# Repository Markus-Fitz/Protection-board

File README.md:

# Protection-board
 Speaker-protection board for power amplifier.

# Description
 The board includes a relay that connects or disconnects the speakers from the amplifiers. The circuit includes a delay function to avoid initial transients to damage the speakers, a DC-detection to protect the speakers in case of a failing output stage or wrong DC-adjustment and a temperature-sensing circuit which disconnects the speakers from the amplifiers in case of overtemperature.

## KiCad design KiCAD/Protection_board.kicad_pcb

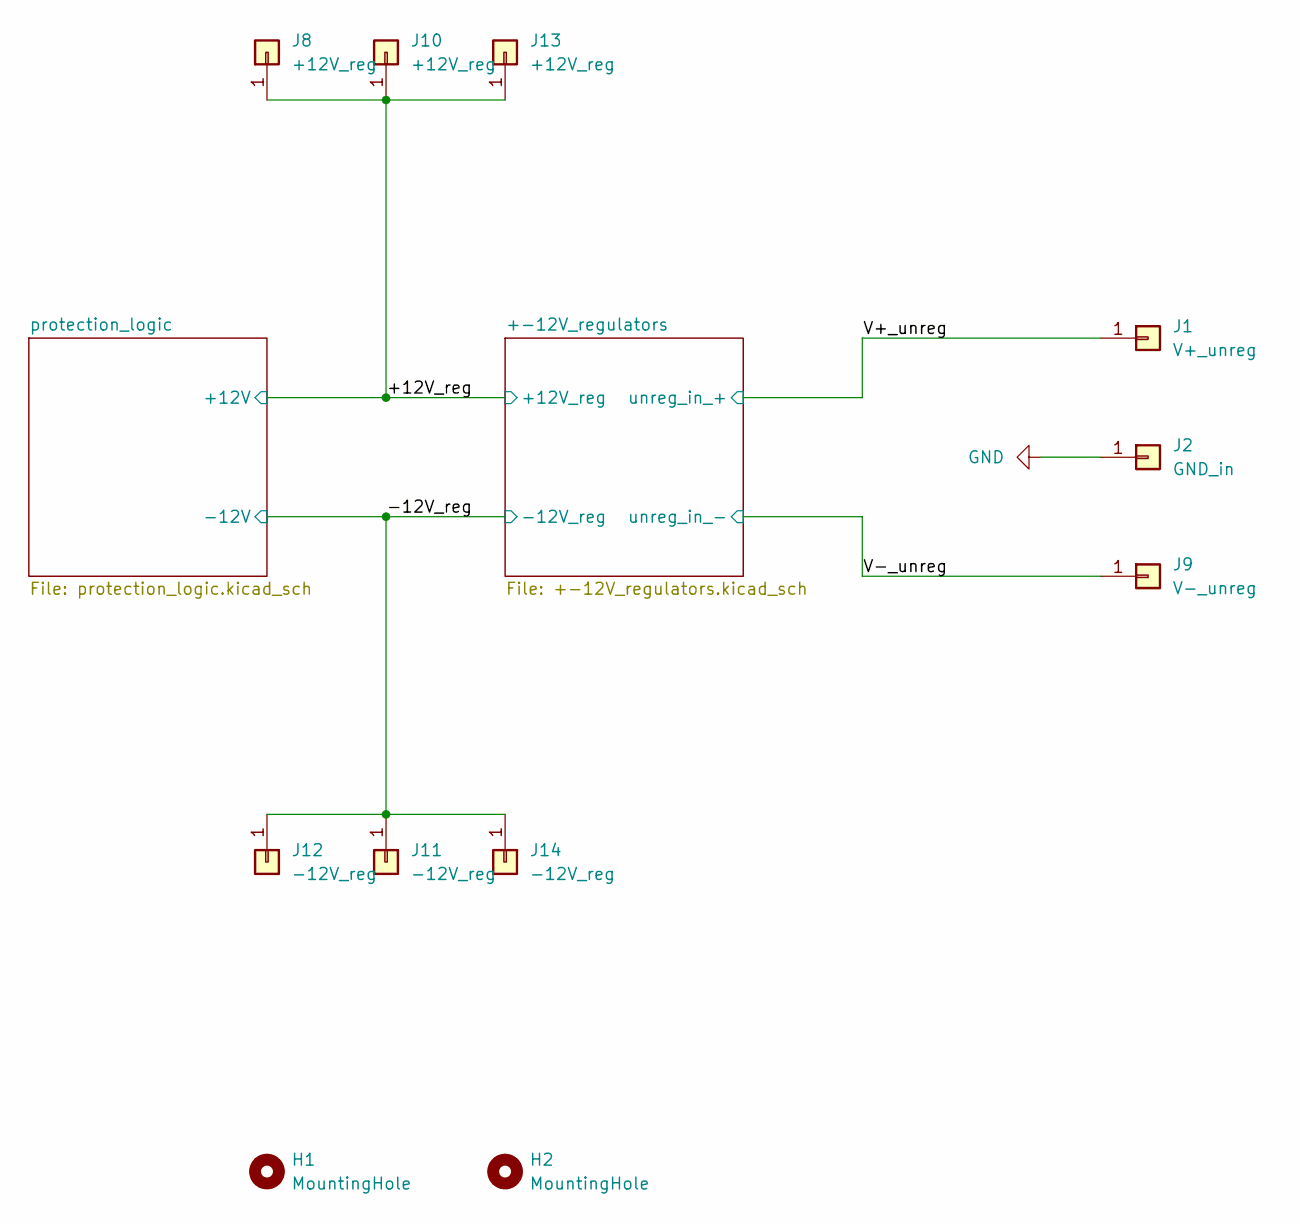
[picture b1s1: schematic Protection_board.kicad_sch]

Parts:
H1, H2: MountingHole; MountingHole_3.2mm_M3
J1: V+_unreg; SolderWire-0.5sqmm_1x01_D0.9mm_OD2.1mm
J2: GND_in; SolderWire-0.5sqmm_1x01_D0.9mm_OD2.1mm
J8, J10, J13: +12V_reg; SolderWire-0.5sqmm_1x01_D0.9mm_OD2.1mm
J9: V-_unreg; SolderWire-0.5sqmm_1x01_D0.9mm_OD2.1mm
J11, J12, J14: -12V_reg; SolderWire-0.5sqmm_1x01_D0.9mm_OD2.1mm

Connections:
/+12V_reg: J8.1, J10.1, J13.1; also elsewhere on the board
/-12V_reg: J11.1, J12.1, J14.1; also elsewhere on the board
/V+_unreg: J1.1; also elsewhere on the board
/V-_unreg: J9.1; also elsewhere on the board
GND: J2.1; also elsewhere on the board

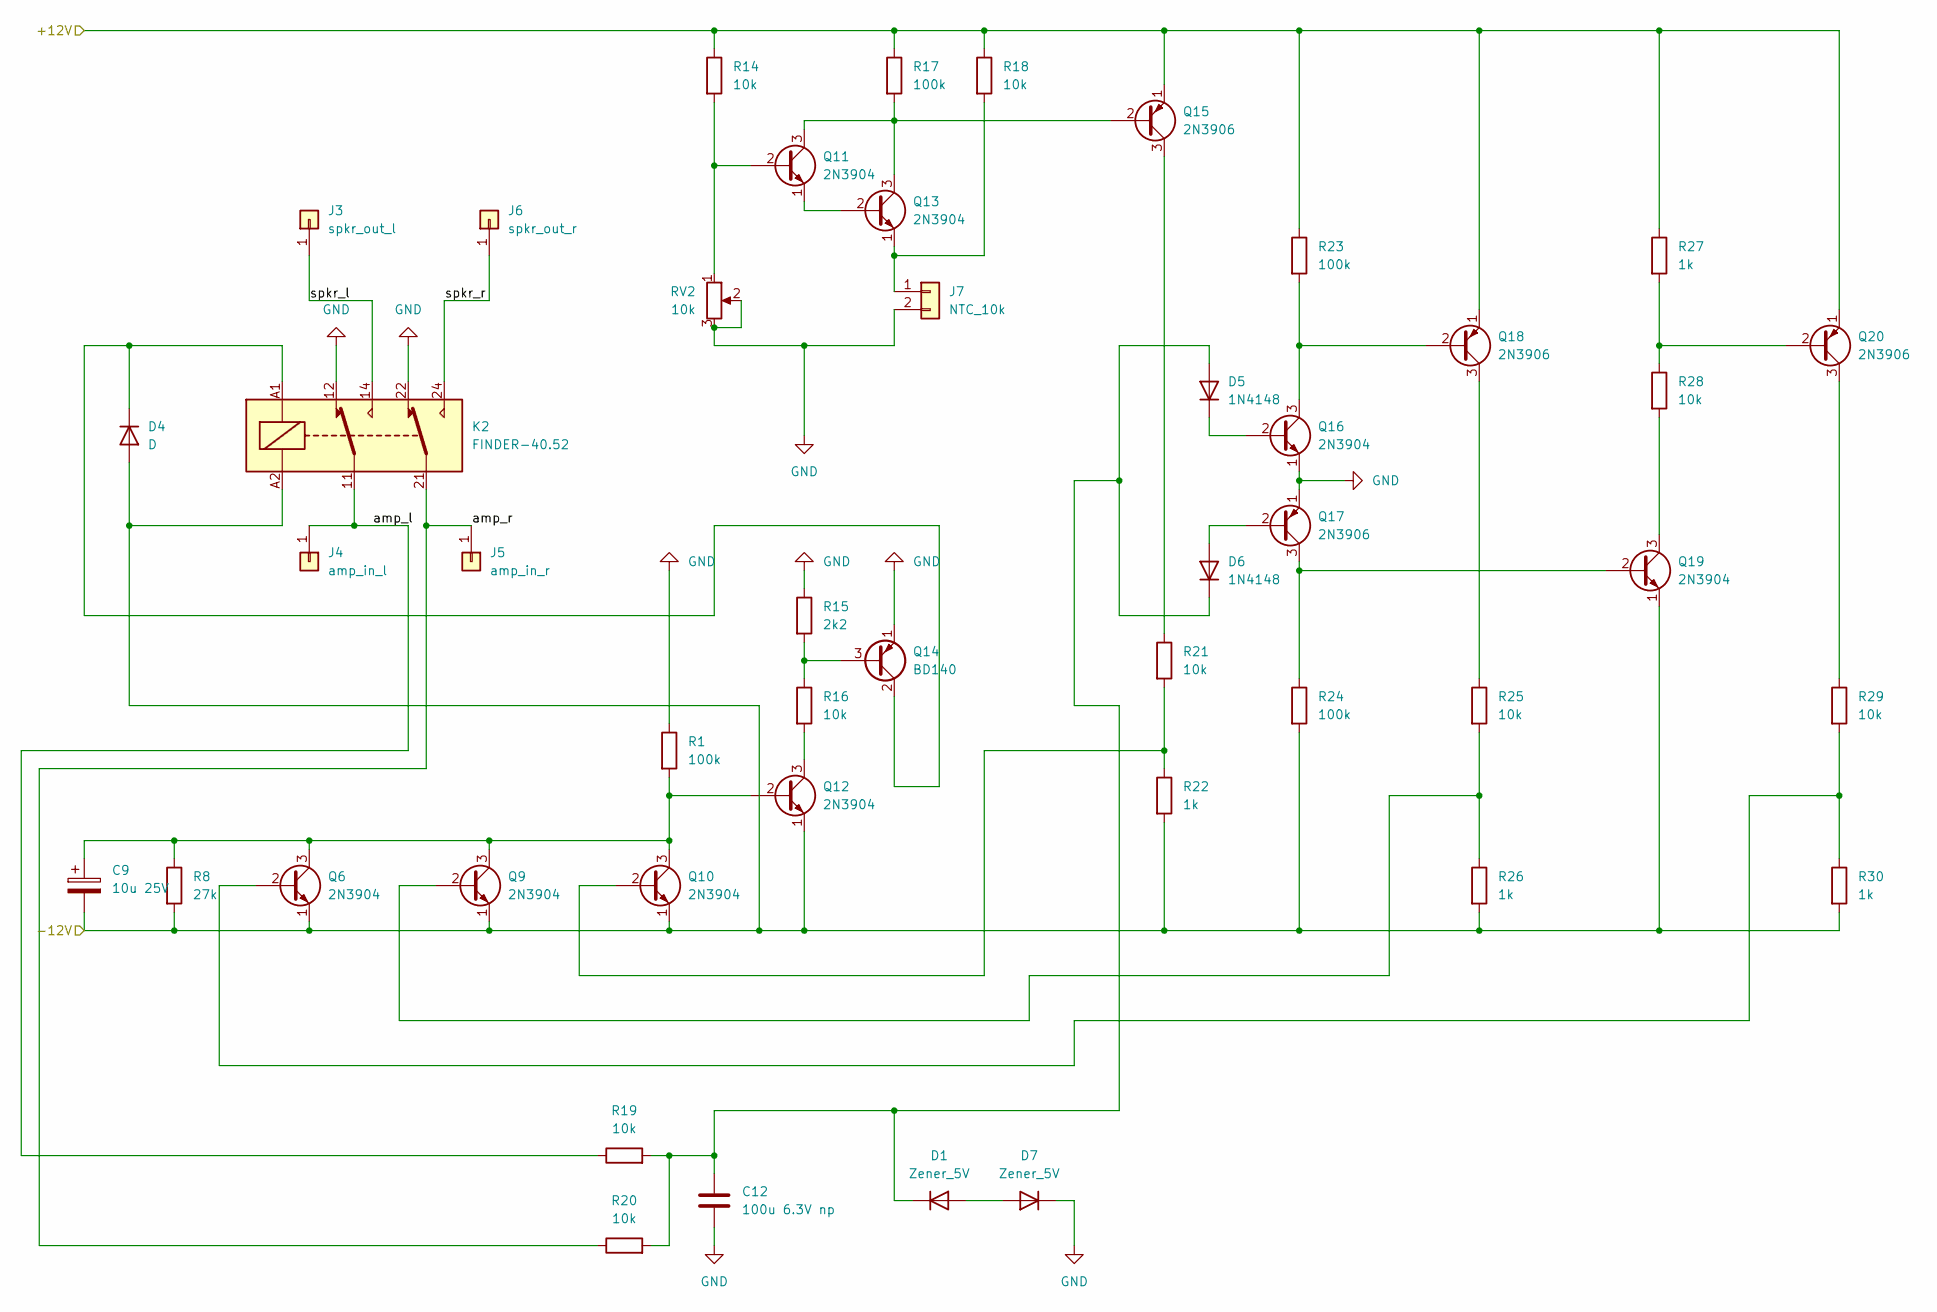
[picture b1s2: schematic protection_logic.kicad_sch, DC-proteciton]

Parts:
C9: 10u 25V; CP_Radial_D5.0mm_P2.00mm
C12: 100u 6.3V np; C_Radial_D8.0mm_H11.5mm_P3.50mm
D1, D7: Zener_5V; D_DO-35_SOD27_P2.54mm_Vertical_AnodeUp
D4: D; D_DO-41_SOD81_P7.62mm_Horizontal
D5, D6: 1N4148; D_DO-35_SOD27_P2.54mm_Vertical_AnodeUp
J3: spkr_out_l; SolderWire-0.5sqmm_1x01_D0.9mm_OD2.1mm
J4: amp_in_l; SolderWire-0.5sqmm_1x01_D0.9mm_OD2.1mm
J5: amp_in_r; SolderWire-0.5sqmm_1x01_D0.9mm_OD2.1mm
J6: spkr_out_r; SolderWire-0.5sqmm_1x01_D0.9mm_OD2.1mm
J7: NTC_10k; SolderWire-0.5sqmm_1x02_P4.6mm_D0.9mm_OD2.1mm
K2: FINDER-40.52; Relay_DPDT_Finder_40.52
Q6, Q9, Q10, Q11, Q12, Q13, Q16, Q19: 2N3904; TO-92_Inline_Wide
Q14: BD140; TO-126-3_Vertical
Q15, Q17, Q18, Q20: 2N3906; TO-92_Inline_Wide
R1, R17, R23, R24: 100k; r_vertical_symm
R8: 27k; r_vertical_symm
R14, R16, R18, R19, R20, R21, R25, R28, R29: 10k; r_vertical_symm
R15: 2k2; r_vertical_symm
R22, R26, R27, R30: 1k; r_vertical_symm
RV2: 10k; Potentiometer_Bourns_3296W_Vertical

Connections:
/+12V_reg: Q15.1 (E), Q18.1 (E), Q20.1 (E), R14.1, R17.1, R18.1, R23.1, R27.1; also elsewhere on the board
/-12V_reg: C9.2, D4.2 (A), K2.A2, Q6.1 (E), Q9.1 (E), Q10.1 (E), Q12.1 (E), Q19.1 (E), R8.2, R22.2, R24.2, R26.2, R30.2; also elsewhere on the board
/protection_logic/amp_l: J4.1, K2.11, R19.1
/protection_logic/amp_r: J5.1, K2.21, R20.1
/protection_logic/spkr_l: J3.1, K2.14
/protection_logic/spkr_r: J6.1, K2.24
GND: C12.2, D7.1 (K), J7.2, K2.12, K2.22, Q14.1 (E), Q16.1 (E), Q17.1 (E), R1.1, R15.1, RV2.2, RV2.3; also elsewhere on the board
unnamed: C9.1, Q6.3 (C), Q9.3 (C), Q10.3 (C), Q12.2 (B), R1.2, R8.1
unnamed: C12.1, D1.1 (K), D5.2 (A), D6.1 (K), R19.2, R20.2
unnamed: D1.2 (A), D7.2 (A)
unnamed: D4.1 (K), K2.A1, Q14.2 (C)
unnamed: D5.1 (K), Q16.2 (B)
unnamed: D6.2 (A), Q17.2 (B)
unnamed: J7.1, Q13.1 (E), R18.2
unnamed: Q6.2 (B), R29.2, R30.1
unnamed: Q9.2 (B), R25.2, R26.1
unnamed: Q10.2 (B), R21.2, R22.1
unnamed: Q11.1 (E), Q13.2 (B)
unnamed: Q11.2 (B), R14.2, RV2.1
unnamed: Q11.3 (C), Q13.3 (C), Q15.2 (B), R17.2
unnamed: Q12.3 (C), R16.2
unnamed: Q14.3 (B), R15.2, R16.1
unnamed: Q15.3 (C), R21.1
unnamed: Q16.3 (C), Q18.2 (B), R23.2
unnamed: Q17.3 (C), Q19.2 (B), R24.1
unnamed: Q18.3 (C), R25.1
unnamed: Q19.3 (C), R28.2
unnamed: Q20.2 (B), R27.2, R28.1
unnamed: Q20.3 (C), R29.1

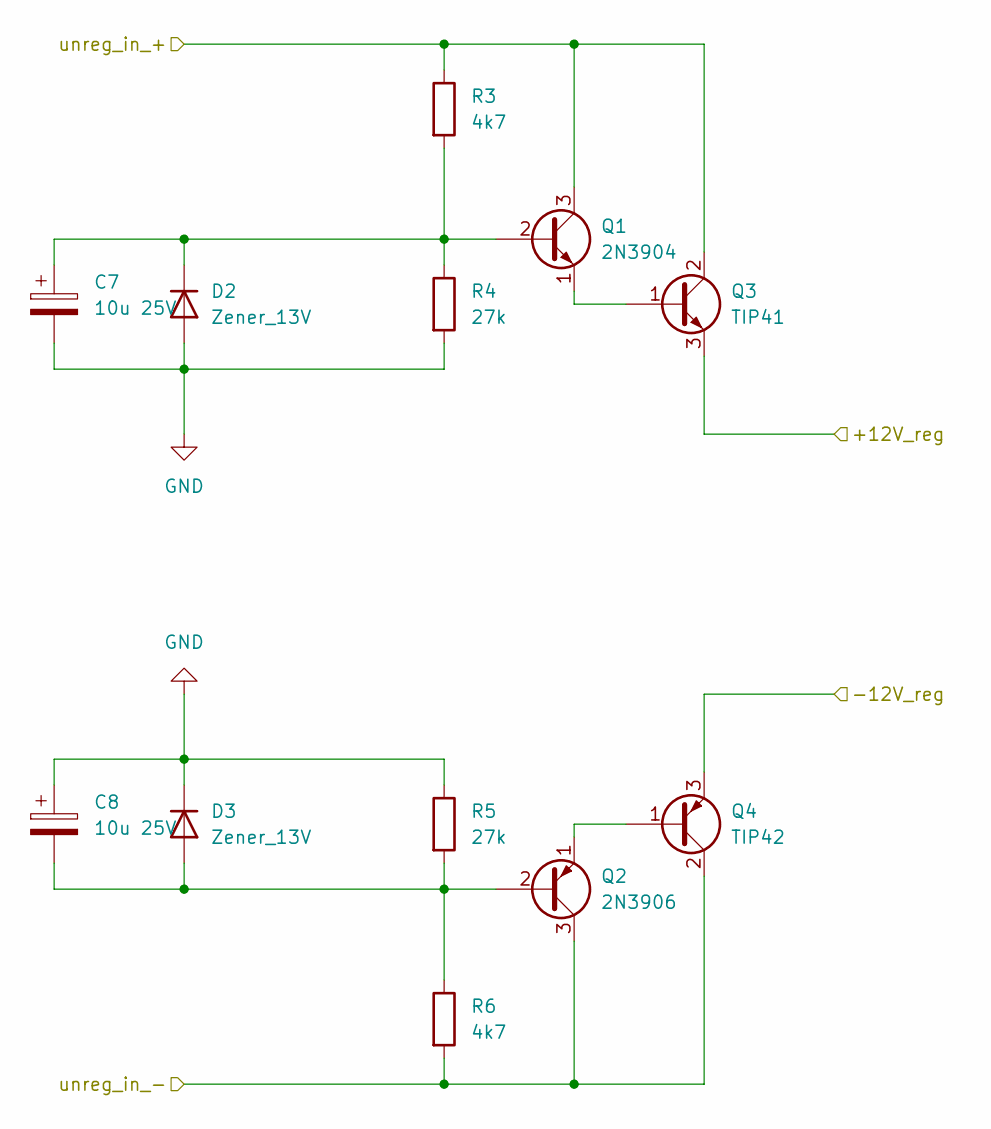
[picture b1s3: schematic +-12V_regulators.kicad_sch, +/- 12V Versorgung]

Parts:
C7, C8: 10u 25V; CP_Radial_D5.0mm_P2.00mm
D2, D3: Zener_13V; D_DO-35_SOD27_P2.54mm_Vertical_AnodeUp
Q1: 2N3904; TO-92_Inline_Wide
Q2: 2N3906; TO-92_Inline_Wide
Q3: TIP41; TO-220-3_Vertical
Q4: TIP42; TO-220-3_Vertical
R3, R6: 4k7; r_vertical_symm
R4, R5: 27k; r_vertical_symm

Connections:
/+12V_reg: Q3.3 (E); also elsewhere on the board
/-12V_reg: Q4.3 (E); also elsewhere on the board
/V+_unreg: Q1.3 (C), Q3.2 (C), R3.1; also elsewhere on the board
/V-_unreg: Q2.3 (C), Q4.2 (C), R6.2; also elsewhere on the board
GND: C7.2, C8.1, D2.2 (A), D3.1 (K), R4.2, R5.1; also elsewhere on the board
unnamed: C7.1, D2.1 (K), Q1.2 (B), R3.2, R4.1
unnamed: C8.2, D3.2 (A), Q2.2 (B), R5.2, R6.1
unnamed: Q1.1 (E), Q3.1 (B)
unnamed: Q2.1 (E), Q4.1 (B)

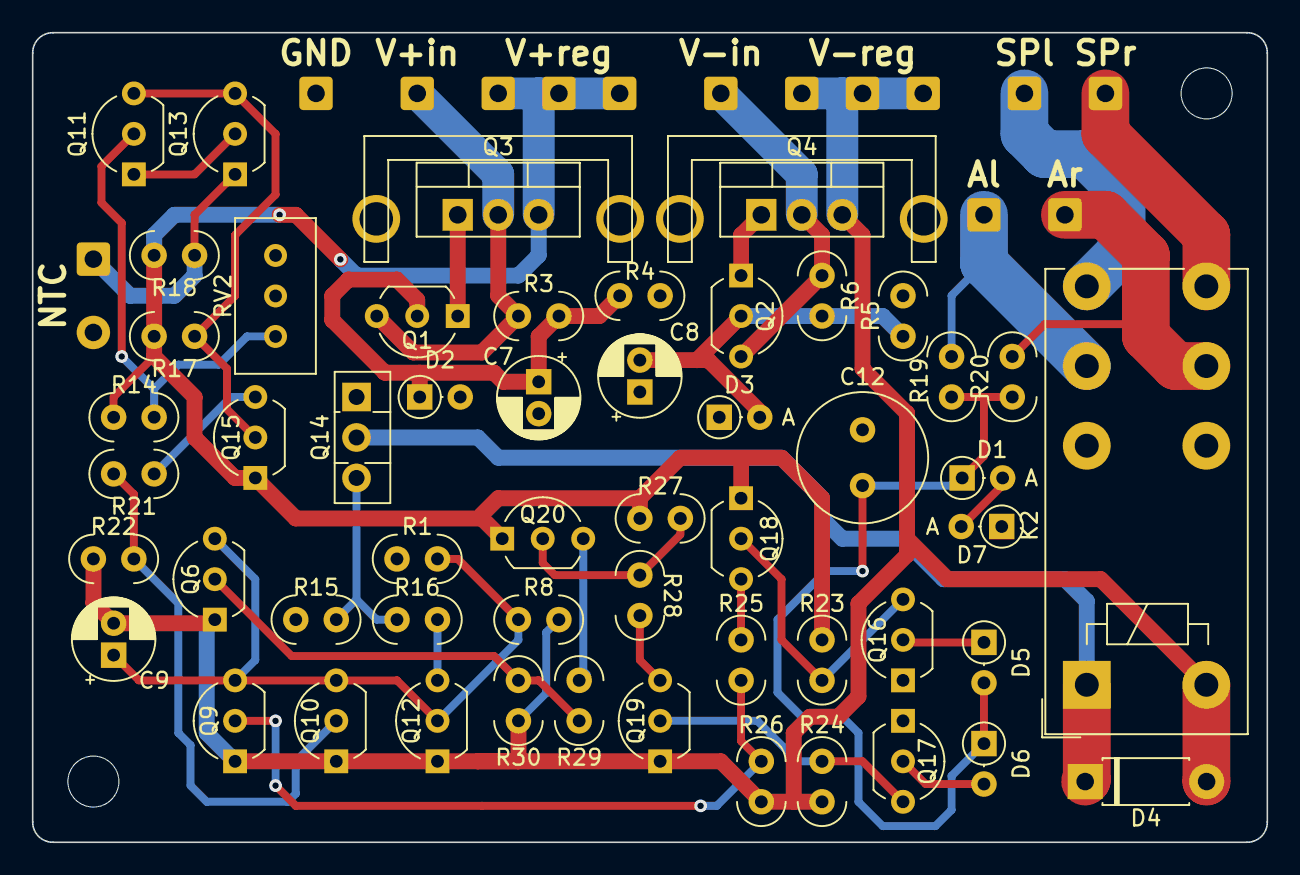
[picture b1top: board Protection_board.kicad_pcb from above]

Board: 2 copper layers, 77.5 x 50.8 mm, 69 parts (0 on the bottom side), 35 nets.

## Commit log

2024-04-08 Modified Readme
    Modification of Readme to include circuit description.
2024-04-08 Addition of project files.
    Addition of KiCAD-project and schematic-pdf.
2024-04-08 Added render.
    Addition of render of top side of the board.
2024-04-08 Renaming of schematic.
    The german "Schaltplan" was translated to "schematic".
